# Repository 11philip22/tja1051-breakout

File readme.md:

# TJA1051 breakout board

A TJA1051T breakout board featuring a header jumper to enable or disable the termination resistor, an aditional header to pull the S pin high or to GND and a regular pinheader on CAN_H and CAN_L

## Changelog
V1.1
- replaced 0402 components with 0603
- improved silkscreen readability

V1
- initial design

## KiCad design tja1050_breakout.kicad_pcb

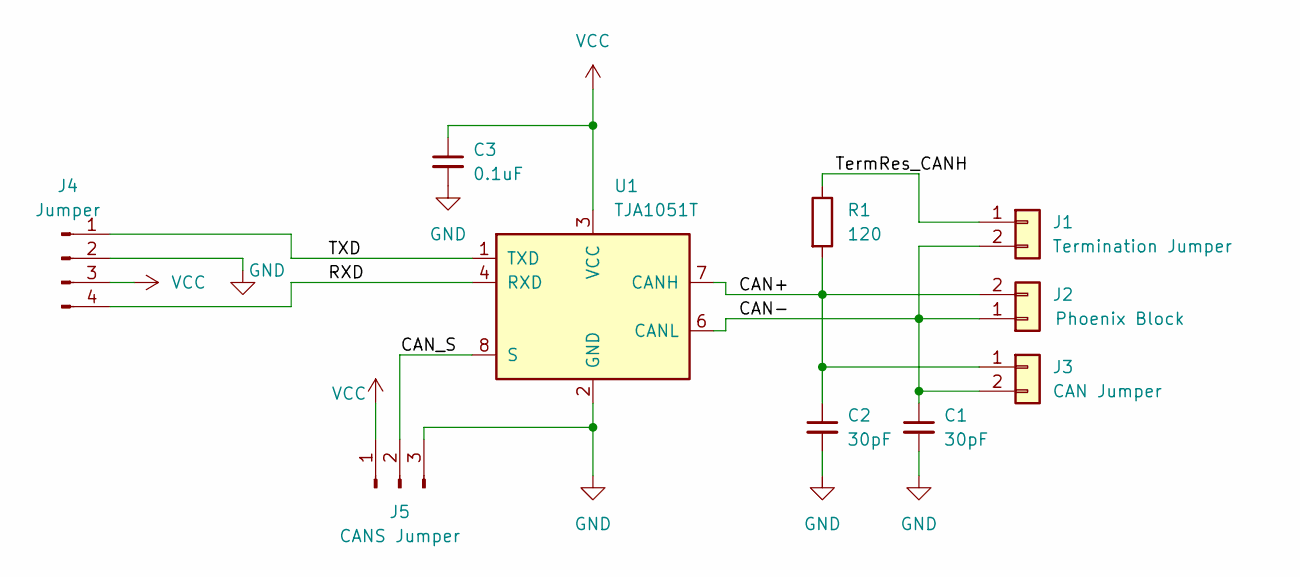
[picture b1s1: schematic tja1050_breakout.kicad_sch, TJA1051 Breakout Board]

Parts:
C1, C2: 30pF; C_0603_1608Metric; LCSC C1658
C3: 0.1uF; C_0603_1608Metric; LCSC C14663
J1: Termination Jumper; PinHeader_1x02_P2.54mm_Vertical; LCSC C32713268
J2: Phoenix Block; TerminalBlock_Phoenix_MKDS-1,5-2-5.08_1x02_P5.08mm_Horizont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; LCSC C474950
J3: CAN Jumper; PinHeader_1x02_P2.54mm_Vertical; LCSC C32713268
J4: Jumper; PinHeader_1x04_P2.54mm_Vertical; LCSC C32713270
J5: CANS Jumper; PinHeader_1x03_P2.54mm_Vertical; LCSC C5360899
R1: 120; R_0603_1608Metric; LCSC C22787
U1: TJA1051T; SOIC-8_3.9x4.9mm_P1.27mm; LCSC C18387

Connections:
/CAN+: C2.1, J2.2, J3.1, R1.2, U1.7 (CANH)
/CAN-: C1.1, J1.2, J2.1, J3.2, U1.6 (CANL)
/CAN_S: J5.2, U1.8 (S)
/RXD: J4.4, U1.4 (RXD)
/TXD: J4.1, U1.1 (TXD)
/TermRes_CANH: J1.1, R1.1
GND: C1.2, C2.2, C3.2, J4.2, J5.3, U1.2 (GND)
VCC: C3.1, J4.3, J5.1, U1.3 (VCC)

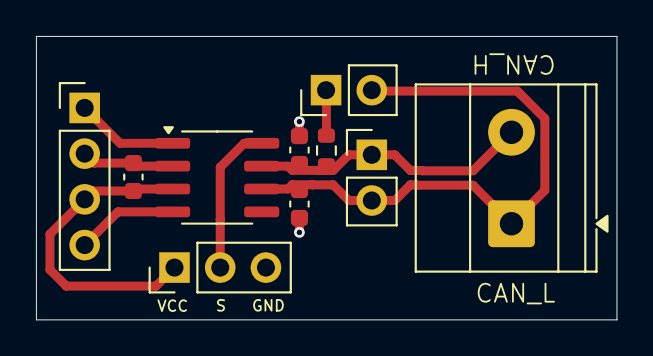
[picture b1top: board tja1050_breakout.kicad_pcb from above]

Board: 2 copper layers, 32.2 x 15.7 mm, 10 parts (0 on the bottom side), 8 nets.

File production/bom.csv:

Designator,Footprint,Quantity,Value,LCSC Part #
"C1, C2",0603,2,30pF,C1658
C3,0603,1,0.1uF,C14663
J1,PinHeader_1x02_P2.54mm_Vertical,1,Termination Jumper,C32713268
J2,"TerminalBlock_Phoenix_MKDS-1,5-2-5.08_1x02_P5.08mm_Horizontal",1,Phoenix Block,C474950
J3,PinHeader_1x02_P2.54mm_Vertical,1,CAN Jumper,C32713268
J4,PinHeader_1x04_P2.54mm_Vertical,1,Jumper,C32713270
J5,PinHeader_1x03_P2.54mm_Vertical,1,CANS Jumper,C5360899
R1,0603,1,120,C22787
U1,SOIC-8_3.9x4.9mm_P1.27mm,1,TJA1051T,C18387

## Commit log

2025-09-24 initial
2025-09-24 add readme
2025-09-24 make loop tighter
2025-09-24 update production
2025-09-26 add vias
2025-09-28 update schematic
2025-09-28 update bom
2025-10-07 v1.1 initial
2025-10-07 v1 images :)
2025-10-07 add board revision
2025-10-11 update mpn
